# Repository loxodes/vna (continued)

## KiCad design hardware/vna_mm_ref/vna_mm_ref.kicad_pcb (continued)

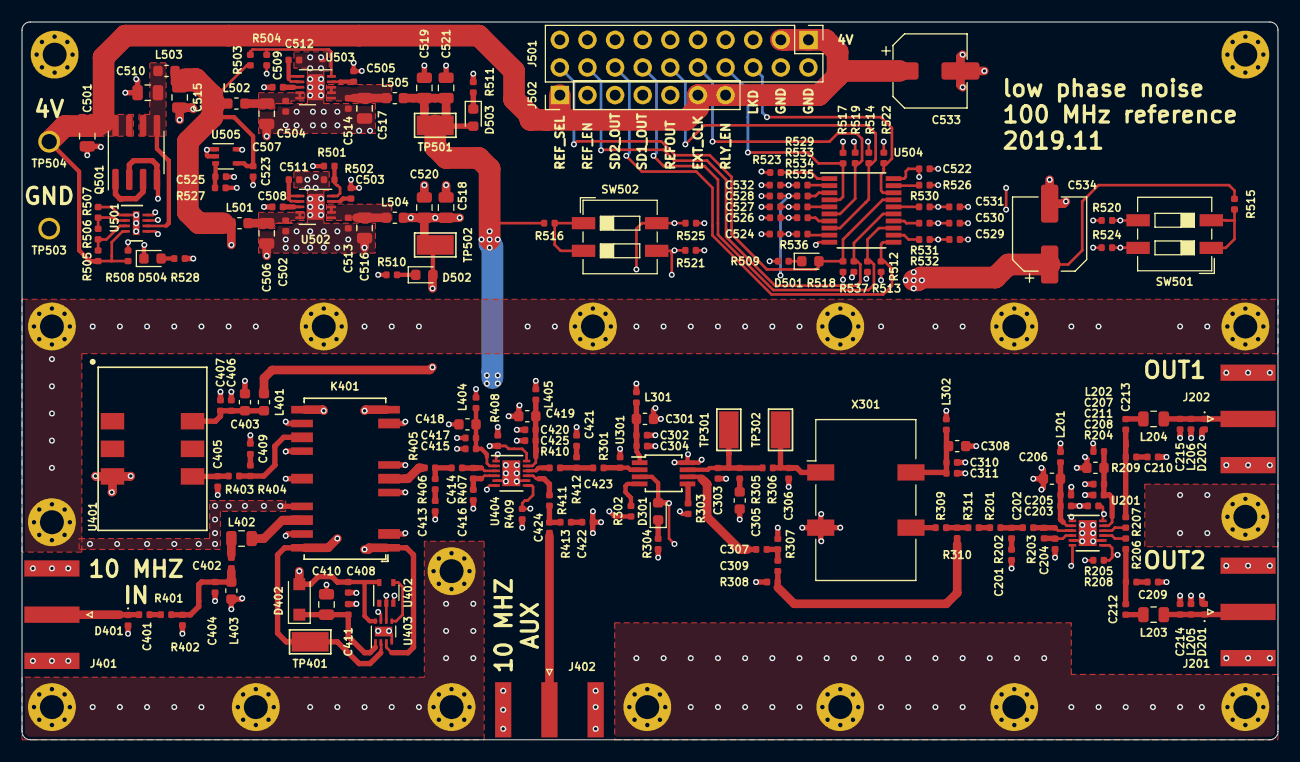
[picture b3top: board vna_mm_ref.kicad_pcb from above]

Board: 4 copper layers, 115.5 x 66.0 mm, 228 parts (0 on the bottom side), 120 nets.

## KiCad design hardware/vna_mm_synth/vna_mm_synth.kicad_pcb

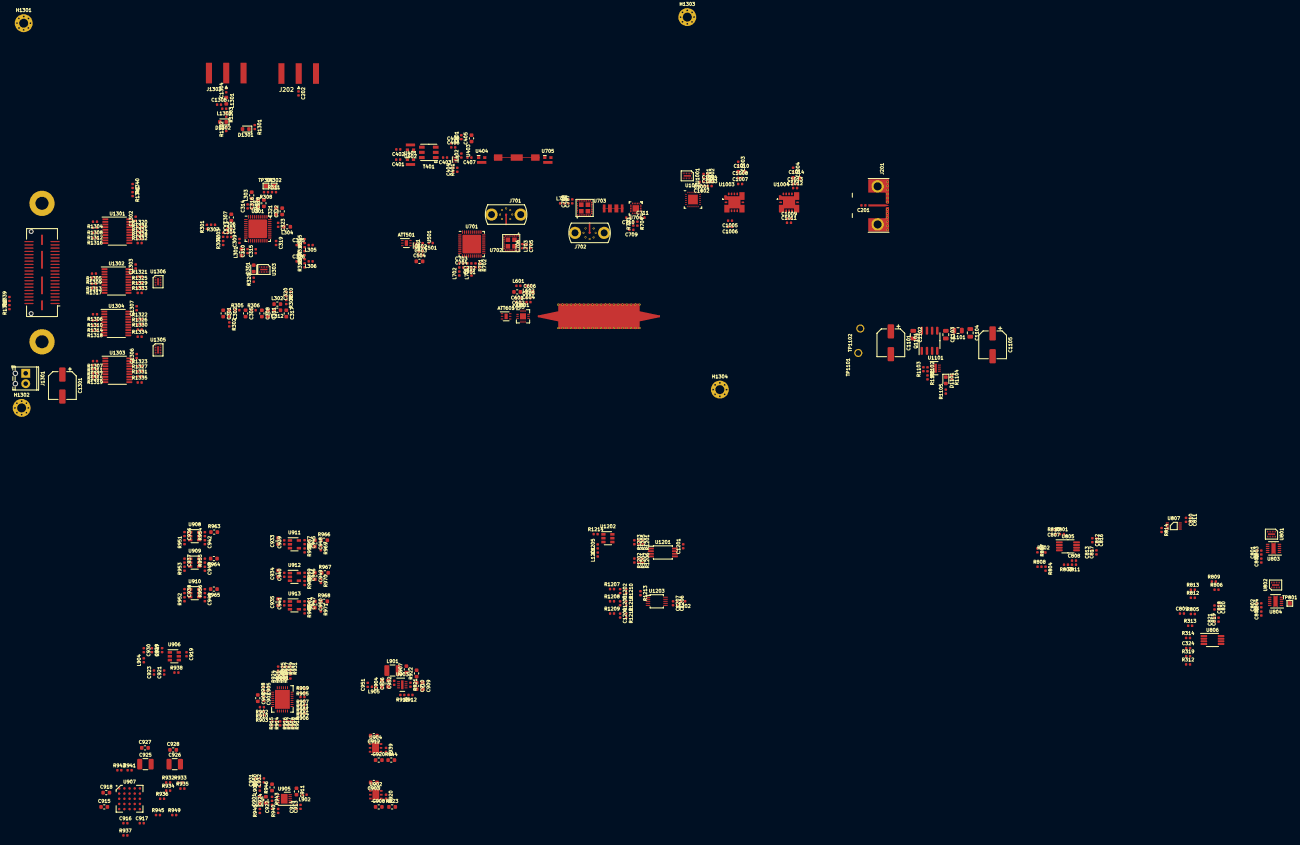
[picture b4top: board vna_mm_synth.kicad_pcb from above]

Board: 6 copper layers, 435 parts (0 on the bottom side), 301 nets, no tracks yet.

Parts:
ATT501: HMC65XLP2E; LP2E_DFN6_2x2mm_Pitch0.60mm
ATT601: TBD_dB; LP2E_DFN6_2x2mm_Pitch0.60mm
C201, C325, C326: 100 nF UWB; C_0402_1005Metric
C202, C303, C304, C319, C408, C503, C602, C605, C701, C704, C705, C708, C801, C802, C811, C816, C817, C820, C821, C902, C905, C916, C917, C921, C929, C932, C939, C940, C941, C951, C952, C1001, C1004, C1006, C1008, C1011, C1013, C1201, C1205, C1206, C1302, C1303, C1306, C1307: 100 nF; C_0402_1005Metric
C301: 390 pF; C_0603_1608Metric
C302: 68 nF; C_0603_1608Metric
C305, C311, C312, C317: DNP; C_0603_1608Metric
C306, C309, C310, C313, C314, C315, C320, C323, C913, C914, C919, C922, C923, C930, C931, C936, C937, C938: 1 uF; C_0402_1005Metric
C307, C316, C318, C321, C322, C915, C918, C924: 10 uF; C_0603_1608Metric
C308: 1800 pF; C_0603_1608Metric
C324, C401, C402, C403, C404, C406, C407, C501, C502, C603, C604, C702, C703, C706, C707, C803, C804, C805, C806, C810, C812, C813, C818, C819, C1002, C1003, C1005, C1007, C1009, C1012: 100 pF; C_0402_1005Metric
C405, C504, C601, C606, C901, C903, C904, C906, C908, C909, C912, C920, C927, C928, C933, C934, C935, C948, C949, C950, C1010, C1014: 2.2 uF; C_0603_1608Metric
C709, C710, C711, C807, C808, C809: 10 pF; C_0402_1005Metric
C907: 220 nF; C_0603_1608Metric
C910: 100 nF; C_0603_1608Metric
C911: 22 uF; C_0603_1608Metric
C925, C926: 47 uF; C_1210_3225Metric
C942, C943, C944: DNI; C_0402_1005Metric
C945, C946, C947: 10 nF; C_0402_1005Metric
C1101, C1105: 330 uF; CP_Elec_6.3x5.9
C1102, C1103, C1104: 22 uF; C_0805_2012Metric
C1202, C1203, C1204, C1207: 1 nF; C_0402_1005Metric
C1301: 330 uF; CP_Elec_6.3x5.8
C1304: 4.5 pF; C_0402_1005Metric
C1305: 220 pF; C_0402_1005Metric
D301: LED_Small; LED_0603_1608Metric
D901, D1101: RED; LED_0603_1608Metric
D1301, D1302: D_TVS; D_0603_1608Metric
FL601: band_pass_filter; band_x2_siw_fr408_6p7mil
FL701: low_pass_filter; stepped_lpf_8ghz_fr408
FL702: low_pass_filter; stepped_lpf_20ghz_fr408
H1301, H1302, H1303, H1304: MountingHole_Pad; MountingHole_2.2mm_M2_Pad_Via
J201: Conn_Coaxial; sw_edge_ro4350b_10mil
J202, J1303: Conn_Coaxial; SMA_Amphenol_132289_EdgeMount
J701, J702: Conn_Coaxial; SF2921-61345
J1301: Screw_Terminal_01x02; TerminalBlock_Phoenix_MPT-0,5-2-2.54_1x02_P2.54mm_Horizontal
J1302: SYZYGY-STD; SYZYGY_standard_carrier
L301, L303, L304: TBD_FERRITE; L_0603_1608Metric
L302: JMP; L_0603_1608Metric
L305, L306, L401, L402, L501, L601, L602, L701, L702, L703, L704, L904, L1001, L1002, L1003, L1004, L1201, L1202: BLM15GG471; L_0402_1005Metric
L901: 15 uH; L_1210_3225Metric
L902, L903, L905: BLM15AG102SZ1D; L_0402_1005Metric
L1101: TBD; L_0805_2012Metric
L1301: 560 nH; L_0603_1608Metric
L1302: 11 nH; L_0402_1005Metric
Q1101: FDS6890A; SOIC-8_3.9x4.9mm_P1.27mm
R301, R902, R903, R908, R910, R913, R936, R937, R947, R1201, R1203, R1205, R1210, R1211, R1212, R1301, R1302: DNI; R_0402_1005Metric
R302: 68; R_0402_1005Metric
R303: 100; R_0402_1005Metric
R304: DNP; R_0402_1005Metric
R305, R307, R920, R939, R943, R1213, R1214: 0; R_0402_1005Metric
R306: 18; R_0402_1005Metric
R308, R311, R703, R704, R938, R940, R954, R955, R956: 1k; R_0402_1005Metric
R309, R310, R925, R959: 51k; R_0402_1005Metric
R312, R313, R314, R319, R320, R807, R808, R809, R810, R811, R812, R813, R814, R905, R907, R909, R911, R912, R914, R915, R916, R917, R918, R919, R926, R928, R930, R932, R933, R934, R935, R941, R942, R948, R951, R952, R953, R1105, R1304, R1305, R1306, R1307, R1308, R1309, R1310, R1311, R1312, R1313, R1314, R1315, R1316, R1317, R1318, R1319, R1320, R1321, R1322, R1323, R1324, R1325, R1326, R1327, R1328, R1329, R1330, R1331, R1332, R1333, R1334, R1335, R1336, R1337, R1338, R1339, R1340, R1341: 10k; R_0402_1005Metric
R315, R316, R317, R318: 51; R_0402_1005Metric
R401, R945: 7.5k; R_0402_1005Metric
R701, R702: TBD; R_0402_1005Metric
R801, R802, R803, R804, R805, R806: 33k; R_0402_1005Metric
R901, R904, R906, R924, R1104: 100k; R_0402_1005Metric
R921: 2.21M; R_0402_1005Metric
R922, R923, R944, R946, R963, R964, R965, R966, R967, R968: 0; R_0603_1608Metric
R927, R929, R958: 21k; R_0402_1005Metric
R931, R960: 47k; R_0402_1005Metric
R949: 12k; R_0402_1005Metric
R950: 10; R_0402_1005Metric
R957, R961: 68k; R_0402_1005Metric
R962: 39k; R_0402_1005Metric
R969, R970, R971: 2k; R_0402_1005Metric
R1101: 1.8M; R_0402_1005Metric
R1102: 60k; R_0402_1005Metric
R1103: 240k; R_0402_1005Metric
R1202, R1204, R1206, R1303: JMP; R_0402_1005Metric
R1207, R1208, R1209: 50k; R_0402_1005Metric
T401: MABA-011082; transformer_3p81_3p81
TP301, TP302, TP801: TestPoint; TestPoint_Pad_1.0x1.0mm
TP1101, TP1102: TestPoint; TURRET_MILLMAX_2101
U301: LMX2595; Texas_S-PVQFN-N40_EP4.6x4.6mm
U303, U801, U802, U1001, U1305, U1306: VEMI65AB-HCI; LLP2513-13L
U401, U402, U404, U705: PAT1220-C-0DB; RF_Attenuator_Susumu_PAT1220
U403: MAAM-011206; TDFN6
U501: MAAM-011101; TDFN6
U601: HMC576LC3B; LC3B
U701: ADMV8416; QFN-40-1EP_6x6mm_P0.5mm_EP4.6x4.6mm
U702, U703: PE42543; RFSW__PE42543A-X
U704: ADRF5020; ADRF5020BCCZN
U803, U804: DAC7563SDSCR; DFN-10_PWSON_N10_3x3mm_P0.5mm_EP1.05x2.55mm
U805, U806: OPA2140; MSOP-8_3x3mm_P0.65mm
U807: TS5A23166; VSSOP-8
U901: LTC2937; QFN-28_EP_6x5_Pitch0.5mm
U902, U904: NCP692; DFN-6-1EP_3x3mm_P0.95mm_EP1.7x2.6mm
U903: LT3494; DFN-8-1EP_2x3mm_P0.5mm_EP0.61x2.2mm
U905: ADP7158; DFN-10-1EP_3x3mm_P0.5mm_EP1.65x2.38mm
U906: LM2776; SOT-23-6
U907: LTM4622A; BGA-25_5x5_6.35x6.35mm
U908, U909, U910: TPS22918; SOT-23-6
U911, U912, U913: TPS72301DB; SOT-23-5
U1002: ADRF5730; LGA-24_EP_4x4_Pitch0.5mm
U1003, U1004: MAAM-011109; MACOM_LGA9
U1101: LTC4365DDB; DFN-8-1EP_2x3mm_P0.5mm_EP0.61x2.2mm
U1201: 24LC512; TSSOP-8_4.4x3mm_P0.65mm
U1202: LM73; SOT-23-6
U1203: ADS1115IDGS; TSSOP-10_3x3mm_P0.5mm
U1301, U1302, U1303, U1304: 74AHC244; TSSOP-20_4.4x6.5mm_P0.65mm

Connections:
+3.3VA: C1201.1, C1302.1, C1303.1, C1306.1, C1307.1, J1302.39, L1201.1, R923.2, R1201.1, R1203.1, R1205.1, U1201.8, U1301.20, U1302.20, U1303.20, U1304.20
+3.3VP: C710.1, C931.2, C932.2, L703.1, L704.1, L1001.1, R950.2, U704.11, U901.28, U1001.5
+3V3: C306.2, C315.2, C319.1, L301.1, L303.1, L304.1, L305.1, L306.1, R946.2, U301.7, U301.15, U301.21
+3V8: C925.1, C927.1, L902.1, R941.2, R942.2, R1105.1, U907.D1, U907.E1
+5VP: C801.2, C802.2, C803.2, C804.2, C810.2, C811.2, C812.2, C816.2, C936.1, C937.1, C938.1, C951.1, L701.1, L905.2, L1003.1, L1004.1, L1202.1, R912.1, R944.2, R1340.1, U803.9, U804.9, U805.8, U807.8, U901.27, U908.1, U909.1, U910.1
+6V: C903.2, C905.2, C912.2, C921.2, C923.2, C926.1, C928.1, R938.1, U901.2, U902.1, U902.6, U904.1, U904.6, U906.3, U907.A1, U907.B1
+9V: C915.1, C918.1, C1104.1, C1105.1, L1101.1, R924.1, R932.1, R934.1, U907.A2, U907.B3, U907.D3, U907.E2
+15V: C818.2, C820.2, R922.2, U806.8
-2V5: C711.1, R927.1, R967.2, U704.15
-3V3: L1002.1, R929.1, R968.2
-5V: C813.2, C817.2, C819.2, C821.2, C1005.1, C1006.1, C1009.1, C1011.1, L702.1, R931.1, R966.2, U805.4, U806.4, U1003.2, U1004.2
/AMP_SCK: U801.10, U802.10, U1301.12
/AMP_SDI: U801.11, U802.11, U1301.3
/AMP_VC_A: U807.1, U1003.9
/AMP_VC_B: U807.5, U1004.9
/AMP_~CLR: R1336.1, U801.8, U802.8, U1301.16
/AMP_~SYNC: U801.9, U1301.18
/ATT_LE: U1001.6, U1304.14
/ATT_SCK: U1001.4, U1304.16
/ATT_SDI: U1001.3, U1304.18
/ATT_SDO: R1318.1, U1001.2, U1304.8
/FILT_BANDSEL: R701.2, U1305.7
/FILT_VTUNE: R813.1, U701.19
/FILT_~SYNC: U802.9, U1305.8
/HIGHBAND_EN: R953.1, U910.3, U1305.10
/HIGHBAND_VX2: L601.1, L602.1, R965.1
/LOWBAND_EN: R951.1, U908.3, U1305.12
/LOWBAND_VAMP: L401.2, R963.1
/MAAM_VC_EN: U801.12, U1305.9
/MIDBAND_EN: R952.1, U909.3, U1305.11
/MIDBAND_VAMP: C502.2, C503.2, C504.2, L501.1, R964.1
/PLL_CE: U303.7, U1303.14
/PLL_CSB: U303.12, U1303.12
/PLL_SCK: U303.8, U1303.16
/PLL_SDI: U303.9, U1303.18
/PLL_SDO: R1323.1, U303.10, U1303.17
/PLL_SYNC: C202.2, R301.2, R307.2
/POW_ON: U901.5, U1306.7
/SCL: J1302.3, R907.2, U901.19, U1201.6, U1202.4, U1203.10
/SDA: J1302.1, R911.2, U901.18, U1201.5, U1202.6, U1203.9
/SW1_V1: U702.28, U1306.12
/SW1_V2: U702.27, U1306.11
/SW2_V1: U703.28, U1306.10
/SW2_V2: U703.27, U1306.9
/SW3_HIGH_SEL: C709.1, R703.1, U1306.8
/VDET_A: R1207.1, U1003.8
/VDET_B: R1208.1, U1004.8
/VTUNE_TLM: R314.1, R319.2, R1209.1
/WP: R905.2, U901.22, U1304.3
/bias_control/DAC_VREF: C805.2, R801.2, R803.2, U803.10
/bias_control/FILT_VOUTA: R806.2, U804.1
/bias_control/FILT_VREF: C806.2, R805.2, U804.10
/bias_control/VC_EN: R814.1, U801.1, U807.3, U807.7
/bias_control/VOUTA: R802.2, R804.2, U803.1
/conn_power/AMP_SCK_UNBUF: J1302.29, R1316.1, U1301.8
/conn_power/AMP_SDI_UNBUF: J1302.31, R1320.1, U1301.17
/conn_power/AMP_~CLR~_UNBUF: J1302.25, R1308.1, U1301.4
/conn_power/AMP_~SYNC~_UNBUF: J1302.23, R1304.1, U1301.2
/conn_power/ATT_LE_UNBUF: J1302.10, R1314.1, U1304.6
/conn_power/ATT_SCK_UNBUF: J1302.8, R1310.1, U1304.4
/conn_power/ATT_SDI_UNBUF: J1302.6, R1306.1, U1304.2
/conn_power/ATT_SDO_UNBUF: J1302.12, U1304.12
/conn_power/CONN_REF_N: J1302.36, R1301.1
/conn_power/CONN_REF_P: J1302.34, R1302.1
/conn_power/EXT_CLK_N: C304.1, D1301.1, R303.1, R304.2, R1301.2
/conn_power/EXT_CLK_P: C303.1, D1302.1, R303.2, R1302.2, R1303.2
/conn_power/FILT_BANDSEL_BUF: U1303.9, U1305.6
/conn_power/FILT_BANDSEL_UNBUF: J1302.21, R1335.1, U1303.11
/conn_power/FILT_~SYNC~_BUF: U1303.7, U1305.5
/conn_power/FILT_~SYNC~_UNBUF: J1302.17, R1331.1, U1303.13
/conn_power/HIGHBAND_EN_BUF: U1304.9, U1305.1
/conn_power/HIGHBAND_EN_UNBUF: J1302.20, R1334.1, U1304.11
/conn_power/IO_EN: R1340.2, R1341.1, U1301.1, U1301.19, U1302.1, U1302.19, U1303.1, U1303.19, U1304.1, U1304.19
/conn_power/LOWBAND_EN_BUF: U1304.5, U1305.3
/conn_power/LOWBAND_EN_UNBUF: J1302.16, R1326.1, U1304.15
/conn_power/MAAM_VC_EN_BUF: R1337.1, U1303.5, U1305.4
/conn_power/MAAM_VC_EN_UNBUF: J1302.15, R1327.1, U1303.15
/conn_power/MIDBAND_EN_BUF: U1304.7, U1305.2
/conn_power/MIDBAND_EN_UNBUF: J1302.18, R1330.1, U1304.13
/conn_power/PLL_CE_UNBUF: J1302.9, R1315.1, U1303.6
/conn_power/PLL_CSB_UNBUF: J1302.11, R1319.1, U1303.8
/conn_power/PLL_SCK_UNBUF: J1302.7, R1311.1, U1303.4
/conn_power/PLL_SDI_UNBUF: J1302.5, R1307.1, U1303.2
/conn_power/PLL_SDO_UNBUF: J1302.13, U1303.3
/conn_power/SEQ_POW_ON_UNFILT: J1302.22, U1306.6
/conn_power/SEQ_WP_UNBUF: J1302.14, R1322.1, U1304.17
/conn_power/SW1_V1_BUF: U1302.18, U1306.1
/conn_power/SW1_V1_UNBUF: J1302.24, R1305.1, U1302.2
/conn_power/SW1_V2_BUF: U1302.16, U1306.2
/conn_power/SW1_V2_UNBUF: J1302.26, R1309.1, U1302.4
/conn_power/SW2_V1_BUF: U1302.14, U1306.3
/conn_power/SW2_V1_UNBUF: J1302.28, R1313.1, U1302.6
/conn_power/SW2_V2_BUF: U1302.12, U1306.4
/conn_power/SW2_V2_UNBUF: J1302.30, R1317.1, U1302.8
/conn_power/SW3_HIGH_SEL_BUF: U1302.3, U1306.5
/conn_power/SW3_HIGH_SEL_UNBUF: J1302.32, R1321.1, U1302.17
/highband/HIGHBAND_RFIN: ATT601.2, U702.17
/highband/HIGHBAND_RFOUT: FL601.2, U704.18
/level_control/LEVEL_RFIN: U704.3, U1002.5
/level_control/LEVEL_RFOUT: C201.2, U1004.5
/lowband/LOWBAND_RFIN_N: C402.2, R316.1, U301.22
/lowband/LOWBAND_RFIN_P: C401.2, R315.2, U301.23
/lowband/LOWBAND_RFOUT: FL701.1, U404.2
/midband/MIDBAND_RFIN: ATT501.2, R317.2, U301.19
/midband/MIDBAND_RFOUT: C501.1, U701.5
/power/3V3_EN: R914.1, R940.1, U901.9, U902.3
/power/3V8_EN: R934.2, R935.1, U907.D2
/power/5V5_EN: R932.2, R933.1, U907.B2
/power/5V_EN: R915.1, U901.10, U904.3
/power/ALERTB: R906.2, U901.15
/power/FAULTB: R904.2, U901.16
/power/M2_5V_EN: R917.1, U901.12, U912.3
/power/M3_5V_EN: R918.1, U901.13, U913.3
/power/M5V_EN: R919.1, U901.14, U911.3
/power/PGOOD_3V8: R941.1, U907.D4
/power/PGOOD_5V5: R942.1, U907.B4
/power/PGOOD_9V: R916.1, U901.11
/power/PMIC_3V3: C901.1, C902.1, R901.1, R904.1, R905.1, R906.1, R907.1, R909.2, R911.1, R914.2, R915.2, R916.2, R917.2, R918.2, R919.2, R926.1, R928.1, R930.1, U901.3
/power/RSTB: R901.2, U901.17
/synth/CE: U301.1, U303.6
/synth/CPOUT: C301.1, C302.1, R305.2, U301.12
/synth/CSB: U301.24, U303.1
/synth/MUXout: D301.2, U301.20, U303.3
/synth/SCK: U301.16, U303.5
/synth/SDI: U301.17, U303.4
/synth/SYNTH_D: R318.1, U301.18
/synth/VTUNE: C312.1, C317.1, L302.2, R309.2, U301.35
GND: ATT501.1, ATT501.3, ATT501.4, ATT501.6, ATT501.7, ATT601.1, ATT601.3, ATT601.4, ATT601.6, ATT601.7, C301.2, C305.2, C306.1, C307.2, C308.2, C309.1, C310.1, C311.2, C313.1, C314.2, C315.1, C316.2, C317.2, C318.2, C319.2, C320.2, C321.2, C322.2, C323.1, C324.2, C325.1, C326.1, C404.1, C405.1, C406.1, C408.1, C502.1, C503.1, C504.1, C601.2, C602.2, C603.2, C604.2, C605.2, C606.2, C701.2, C702.2, C703.2, C704.2, C705.2, C706.2, C707.2, C708.2, C709.2, C710.2, C711.2, C801.1, C802.1, C803.1, C804.1, C805.1, C806.1, C810.1, C811.1, C812.1, C813.1, C816.1, C817.1, C818.1, C819.1, C820.1, C821.1, C901.2, C902.2, C903.1, C904.2, C905.1, C906.2, C907.2, C908.1, C909.2, C910.2, C911.1, C912.1, C913.1, C914.1, C915.2, C916.2, C917.2, C918.2, C920.1, C921.1, C922.1, C923.1, C924.1, C925.2, C926.2, C927.2, C928.2, C929.1, C930.1, C931.1, C932.1, C933.2, C934.2, C935.2, C936.2, C937.2, C938.2, C939.2, C940.2, C941.2, C942.2, C943.2, C944.2, C945.2, C946.2, C947.2, C948.2, C949.2, C950.2, C951.2, C952.2, C1001.2, C1002.2, C1003.2, C1004.2, C1005.2, C1006.2, C1007.2, C1008.2, C1009.2, C1010.2, C1011.2, C1012.2, C1013.2, C1014.2, C1101.2, C1102.2, C1103.2, C1104.2, C1105.2, C1201.2, C1202.2, C1203.2, C1204.2, C1205.2, C1206.2, C1207.2, C1301.2, C1302.2, C1303.2, C1305.1, C1306.2, C1307.2, D1301.2, D1302.2, FL601.3, H1301.1, H1302.1, H1303.1, H1304.1, J201.2, J202.2, J701.2, J702.2, J1301.2, J1302.41, J1303.2, L1302.2, R301.1, R302.2, R304.1, R308.2, R310.1, R311.2, R312.2, R319.1, R320.1, R702.2, R704.2, R807.1, R808.1, R809.1, R814.2, R902.2, R903.2, R908.2, R910.2, R913.2, R925.1, R933.2, R935.2, R936.1, R937.1, R945.2, R947.2, R948.1, R949.2, R951.2, R952.2, R953.2, R958.2, R960.2, R962.2, R969.2, R970.2, R971.2, R1103.1, R1202.2, R1204.2, R1206.2, R1210.2, R1211.2, R1212.2, R1213.1, R1214.1, R1304.2, R1305.2, R1306.2, R1307.2, R1308.2, R1309.2, R1310.2, R1311.2, R1312.2, R1313.2, R1314.2, R1315.2, R1316.2, R1317.2, R1318.2, R1319.2, R1320.2, R1321.2, R1322.2, R1323.2, R1324.2, R1325.2, R1326.2, R1327.2, R1328.2, R1329.2, R1330.2, R1331.2, R1332.2, R1333.2, R1334.2, R1335.2, R1336.2, R1337.2, R1339.2, R1341.2, T401.2, T401.3, T401.4, TP1101.1, U301.2, U301.4, U301.6, U301.13, U301.14, U301.25, U301.28, U301.31, U301.34, U301.39, U301.40, U301.41, U303.13, U401.3, U402.3, U403.2, U403.4, U403.5, U403.7, U404.3, U501.2, U501.4, U501.5, U501.6, U501.7, U601.1, U601.3, U601.7, U601.9, U601.13, U701.1, U701.2, U701.3, U701.4, U701.6, U701.7, U701.8, U701.9, U701.10, U701.12, U701.14, U701.16, U701.17, U701.18, U701.20, U701.21, U701.22, U701.23, U701.24, U701.25, U701.27, U701.28, U701.29, U701.30, U701.31, U701.32, U701.33, U701.34, U701.35, U701.36, U701.37, U701.38, U701.39, U701.40, U701.41, U702.1, U702.3, U702.4, U702.5, U702.6, U702.8, U702.9, U702.10, U702.11, U702.13, U702.14, U702.15, U702.16, U702.18, U702.19, U702.20, U702.21, U702.23, U702.25, U702.26, U702.29, U702.30, U703.1, U703.3, U703.4, U703.5, U703.6, U703.8, U703.9, U703.10, U703.11, U703.13, U703.14, U703.15, U703.16, U703.18, U703.19, U703.20, U703.21, U703.23, U703.25, U703.26, U703.29, U703.30, U704.1, U704.2, U704.4, U704.5, U704.6, U704.7, U704.9, U704.10, U704.13, U704.16, U704.17, U704.19, U704.20, U704.21, U705.3, U801.7, U801.13, U802.7, U802.13, U803.3, U803.11, U804.3, U804.11, U807.4, U901.4, U901.29, U902.2, U902.7, U903.2, U903.9, U904.2, U904.7, U905.11, U906.2, U907.B5, U907.C1, U907.C2, U907.D5, U908.2, U909.2, U910.2, U911.1, U912.1, U913.1, U1001.13, U1002.3, U1002.4, U1002.6, U1002.7, U1002.8, U1002.9, U1002.10, U1002.11, U1002.12, U1002.13, U1002.15, U1002.16, U1002.25, U1003.10, U1004.10, U1101.1, U1101.9, U1201.4, U1201.7, U1202.2, U1203.3, U1301.10, U1302.10, U1303.10, U1304.10, U1305.13, U1306.13
unnamed: ATT501.5, U501.3
unnamed: ATT601.5, U601.2
unnamed: C201.1, J201.1
unnamed: C202.1, J202.1
unnamed: C302.2, R302.1
unnamed: C303.2, U301.8
unnamed: C304.2, U301.9
unnamed: C305.1, R305.1, R306.2
unnamed: C307.1, U301.3
unnamed: C308.1, C311.1, C312.2, L302.1, R306.1
unnamed: C309.2, U301.10
unnamed: C310.2, L301.2, U301.11
unnamed: C313.2, L303.2, U301.37
unnamed: C314.1, U301.38
unnamed: C316.1, U301.36
unnamed: C318.1, U301.33
unnamed: C320.1, R309.1, R310.2, U806.5
unnamed: C321.1, U301.29
unnamed: C322.1, U301.27
unnamed: C323.2, L304.2, U301.26
unnamed: C324.1, R313.1, R314.2, U806.7
unnamed: C325.2, L305.2, R315.1, R316.2
unnamed: C326.2, L306.2, R317.1, R318.2
unnamed: C401.1, U401.1
unnamed: C402.1, U402.2
unnamed: C403.1, U403.3
unnamed: C403.2, T401.1
unnamed: C404.2, R401.2, U403.6
unnamed: C405.2, C406.2, C408.2, L401.1, L402.2, R401.1
unnamed: C407.1, U404.1
unnamed: C407.2, L402.1, U403.1
unnamed: C501.2, L501.2, U501.1
unnamed: C601.1, C602.1, C603.1, L601.2, U601.12
unnamed: C604.1, C605.1, C606.1, L602.2, U601.10
unnamed: C701.1, C702.1, L701.2, U701.13
unnamed: C703.1, C704.1, L702.2, U701.11
unnamed: C705.1, C706.1, L703.2, U702.24
unnamed: C707.1, C708.1, L704.2, U703.24
unnamed: C807.1, R801.1, R810.2, U805.2
unnamed: C807.2, R810.1, U805.1, U807.2
unnamed: C808.1, R803.1, R811.2, U805.6
unnamed: C808.2, R811.1, U805.7, U807.6
unnamed: C809.1, R805.1, R812.2, U806.2
unnamed: C809.2, R812.1, R813.2, U806.1
unnamed: C904.1, C906.1, C952.1, L901.1, L905.1, U903.3
unnamed: C907.1, U903.8
unnamed: C908.2, R920.2, R923.1, U902.4
unnamed: C909.1, C910.1, R921.1, R922.1, U903.7
unnamed: C911.2, L902.2, U905.9, U905.10
unnamed: C913.2, U905.8
unnamed: C914.2, U905.6, U905.7
unnamed: C916.1, U907.E3
unnamed: C917.1, U907.A3
unnamed: C919.1, U906.6
unnamed: C919.2, U906.5
unnamed: C920.2, R939.2, R944.1, U904.4
unnamed: C922.2, U905.4
unnamed: C924.2, D901.2, L903.1, R943.1, R946.1, U905.1, U905.2
unnamed: C929.2, C930.2, L904.2, R947.1, U906.1
unnamed: C942.1, U908.4
unnamed: C943.1, U909.4
unnamed: C944.1, U910.4
unnamed: C945.1, C948.1, R957.1, R966.1, R969.1, U911.5
unnamed: C946.1, C949.1, R959.1, R967.1, R970.1, U912.5
unnamed: C947.1, C950.1, R961.1, R968.1, R971.1, U913.5
unnamed: C1001.1, C1002.1, L1001.2, U1002.18
unnamed: C1003.1, C1004.1, L1002.2, U1002.17
unnamed: C1007.1, C1008.1, C1010.1, L1003.2, U1003.6
unnamed: C1012.1, C1013.1, C1014.1, L1004.2, U1004.6
unnamed: C1103.1, L1101.2, Q1101.5, Q1101.6, U1101.6
unnamed: C1202.1, R1207.2, R1210.1, U1203.4
unnamed: C1203.1, R1208.2, R1211.1, U1203.5
unnamed: C1204.1, R1209.2, R1212.1, U1203.7
unnamed: C1205.1, L1201.2, U1202.3
unnamed: C1206.1, C1207.1, L1202.2, U1203.8
unnamed: C1304.1, L1301.1
unnamed: C1304.2, J1303.1
unnamed: C1305.2, L1301.2, L1302.1, R1303.1
unnamed: D301.1, R320.2
unnamed: D901.1, R948.2
unnamed: D1101.1, U1101.7
unnamed: D1101.2, R1105.2
unnamed: FL601.1, U601.8
unnamed: FL701.2, U705.1
unnamed: FL702.1, U703.12
unnamed: FL702.2, U704.8
unnamed: J701.1, U702.7
unnamed: J702.1, U703.7
unnamed: J1302.2, R1338.1
unnamed: J1302.4, R1338.2, R1339.1
unnamed: L901.2, U903.1
unnamed: L903.2, R950.1
unnamed: Q1101.1, Q1101.3
unnamed: Q1101.2, Q1101.4, U1101.5
unnamed: R307.1, U301.5
unnamed: R308.1, TP301.1, U301.32
unnamed: R311.1, TP302.1, U301.30
unnamed: R312.1, R313.2, U806.6
unnamed: R701.1, R702.1, U701.15
unnamed: R703.2, U704.12
unnamed: R704.1, U704.14
unnamed: R802.1, R807.2, U805.3
unnamed: R804.1, R808.2, U805.5
unnamed: R806.1, R809.2, U806.3
unnamed: R902.1, U901.6
unnamed: R903.1, U901.8
unnamed: R908.1, U901.1
unnamed: R909.1, U901.21
unnamed: R910.1, U901.7
unnamed: R912.2, R913.1, U903.5
unnamed: R920.1, U902.5
unnamed: R921.2, U903.6
unnamed: R924.2, R925.2, U901.26
unnamed: R926.2, R927.2, U901.25
unnamed: R928.2, R929.2, U901.24
unnamed: R930.2, R931.2, U901.23
unnamed: R936.2, U907.C5
unnamed: R937.2, U907.C4
unnamed: R938.2, U906.4
unnamed: R939.1, U904.5
unnamed: R940.2, U905.5
unnamed: R943.2, U905.3
unnamed: R945.1, U907.A4
unnamed: R949.1, U907.E4
unnamed: R954.1, U908.5
unnamed: R954.2, R963.2, U908.6
unnamed: R955.1, U909.5
unnamed: R955.2, R964.2, U909.6
unnamed: R956.1, U910.5
unnamed: R956.2, R965.2, U910.6
unnamed: R957.2, R958.1, U911.4
unnamed: R959.2, R960.1, U912.4
unnamed: R961.2, R962.1, U913.4
unnamed: R1101.1, R1102.2, U1101.3
unnamed: R1102.1, R1103.2, U1101.2
unnamed: R1104.1, U1101.8
unnamed: R1201.2, R1202.1, U1201.1
unnamed: R1203.2, R1204.1, U1201.2
unnamed: R1205.2, R1206.1, U1201.3
unnamed: R1213.2, U1203.1
unnamed: R1214.2, U1202.1
unnamed: R1312.1, U1301.6
unnamed: R1324.1, U1301.15
unnamed: R1325.1, U1302.15
unnamed: R1328.1, U1301.13
unnamed: R1329.1, U1302.13
unnamed: R1332.1, U1301.11
unnamed: R1333.1, U1302.11
unnamed: T401.5, U402.1
unnamed: T401.6, U401.2
unnamed: TP801.1, U804.2
unnamed: U701.26, U702.12
unnamed: U702.2, U703.22
unnamed: U703.17, U705.2
unnamed: U801.2, U803.8
unnamed: U801.3, U803.7
unnamed: U801.4, U803.6
unnamed: U801.5, U803.5
unnamed: U801.6, U803.4
unnamed: U802.2, U804.8
unnamed: U802.3, U804.7
unnamed: U802.4, U804.6
unnamed: U802.5, U804.5
unnamed: U802.6, U804.4
unnamed: U1001.7, U1002.1
unnamed: U1001.8, U1002.2
unnamed: U1001.9, U1002.24
unnamed: U1001.10, U1002.23
unnamed: U1001.11, U1002.22
unnamed: U1002.14, U1003.1
unnamed: U1003.5, U1004.1
VPP: C1101.1, C1102.1, C1301.1, J1301.1, J1302.33, J1302.35, J1302.37, J1302.38, Q1101.7, Q1101.8, R1101.2, R1104.2, TP1102.1, U1101.4
VSS: C933.1, C934.1, C935.1, C939.1, C940.1, C941.1, L904.1, U911.2, U912.2, U913.2
